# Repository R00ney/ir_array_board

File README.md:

ir_array_board
==============

Eagle files for the ir array board for the NCSU IEEE 2014 SoutheastCon robot

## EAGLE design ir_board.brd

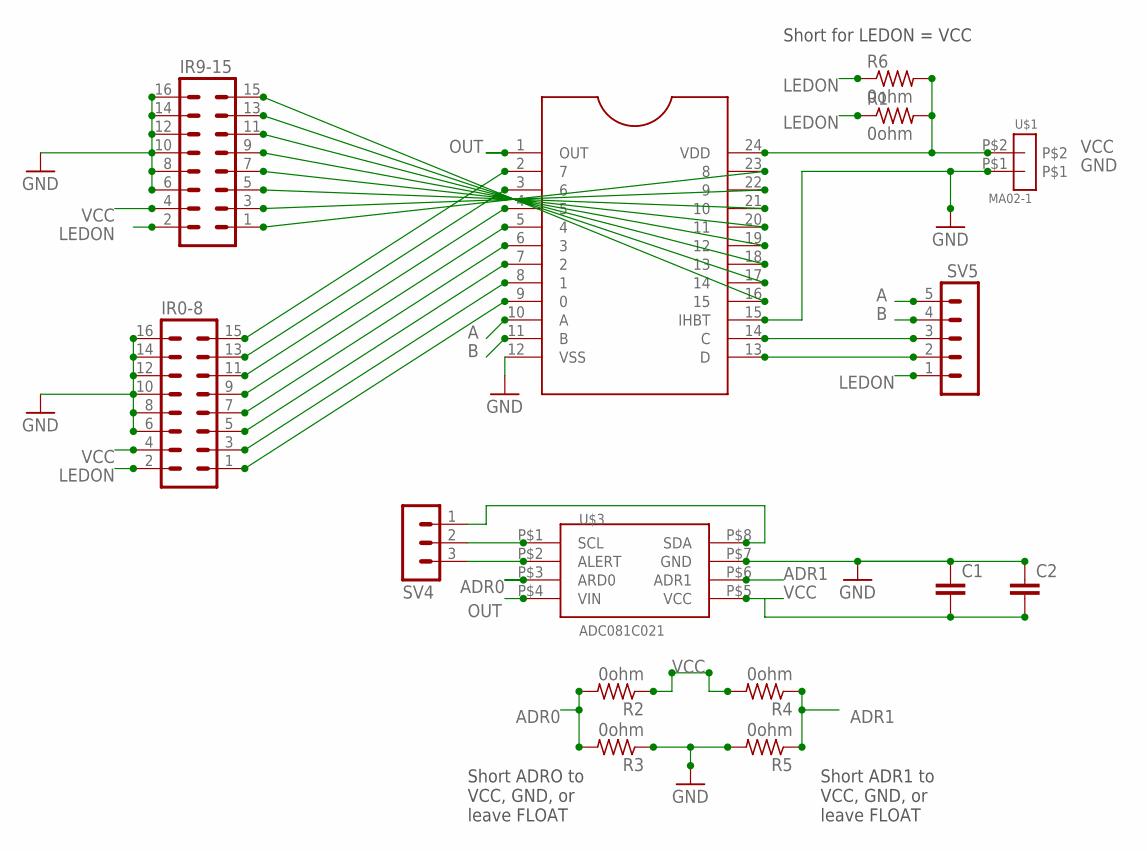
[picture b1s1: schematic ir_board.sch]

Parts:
C1, C2: C-EUC0805K; C0805K
IR0-8, IR9-15: MA08-2
R1, R2, R3, R4, R5, R6: 0ohm; R0805
SV4: MA03-1
SV5: MA05-1
U$1: MA02-1
U$2: 16BIT_ANALOG_MUX; DIL24-6
U$3: ADC081C021; TSSOP-8

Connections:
A: SV5.5, U$2.10 (A)
ADR0: R2.2, R3.2, U$3.P$3 (ARD0)
ADR1: R4.1, R5.1, U$3.P$6 (ADR1)
ALERT: SV4.3, U$3.P$2 (ALERT)
B: SV5.4, U$2.11 (B)
GND: C1.1, C2.1, IR0-8.6, IR0-8.8, IR0-8.10, IR0-8.12, IR0-8.14, IR0-8.16, IR9-15.6, IR9-15.8, IR9-15.10, IR9-15.12, IR9-15.14, IR9-15.16, R3.1, R5.2, U$1.P$1, U$2.12 (VSS), U$2.15 (IHBT), U$3.P$7 (GND)
LEDON: IR0-8.2, IR9-15.2, R1.1, R6.1, SV5.1
unnamed: IR0-8.1, U$2.9 (0)
unnamed: IR0-8.3, U$2.8 (1)
unnamed: IR0-8.5, U$2.7 (2)
unnamed: IR0-8.7, U$2.6 (3)
unnamed: IR0-8.9, U$2.5 (4)
unnamed: IR0-8.11, U$2.4 (5)
unnamed: IR0-8.13, U$2.3 (6)
unnamed: IR0-8.15, U$2.2 (7)
unnamed: IR9-15.1, U$2.23 (8)
unnamed: IR9-15.3, U$2.22 (9)
unnamed: IR9-15.5, U$2.21 (10)
unnamed: IR9-15.7, U$2.20 (11)
unnamed: IR9-15.9, U$2.19 (12)
unnamed: IR9-15.11, U$2.18 (13)
unnamed: IR9-15.13, U$2.17 (14)
unnamed: IR9-15.15, U$2.16 (15)
unnamed: SV5.2, U$2.13 (D)
unnamed: SV5.3, U$2.14 (C)
OUT: U$2.1 (OUT), U$3.P$4 (VIN)
SCL: SV4.2, U$3.P$1 (SCL)
SDA: SV4.1, U$3.P$8 (SDA)
VCC: C1.2, C2.2, IR0-8.4, IR9-15.4, R1.2, R2.1, R4.2, R6.2, U$1.P$2, U$2.24 (VDD), U$3.P$5 (VCC)

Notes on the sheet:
Short for LEDON = VCC
Short ADRO to VCC, GND, or leave FLOAT
Short ADR1 to VCC, GND, or leave FLOAT

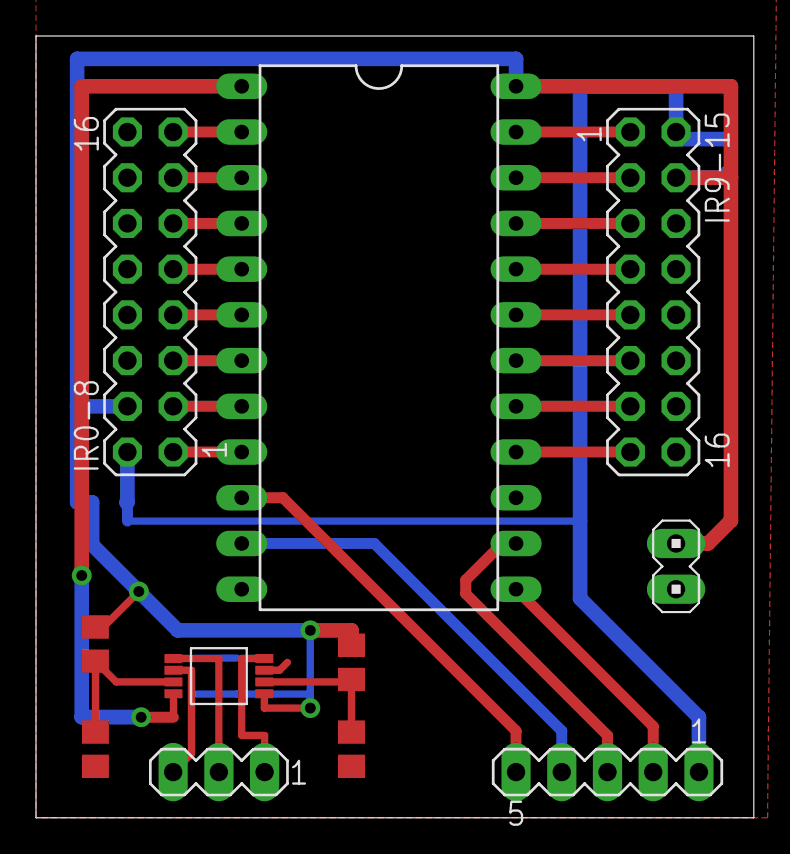
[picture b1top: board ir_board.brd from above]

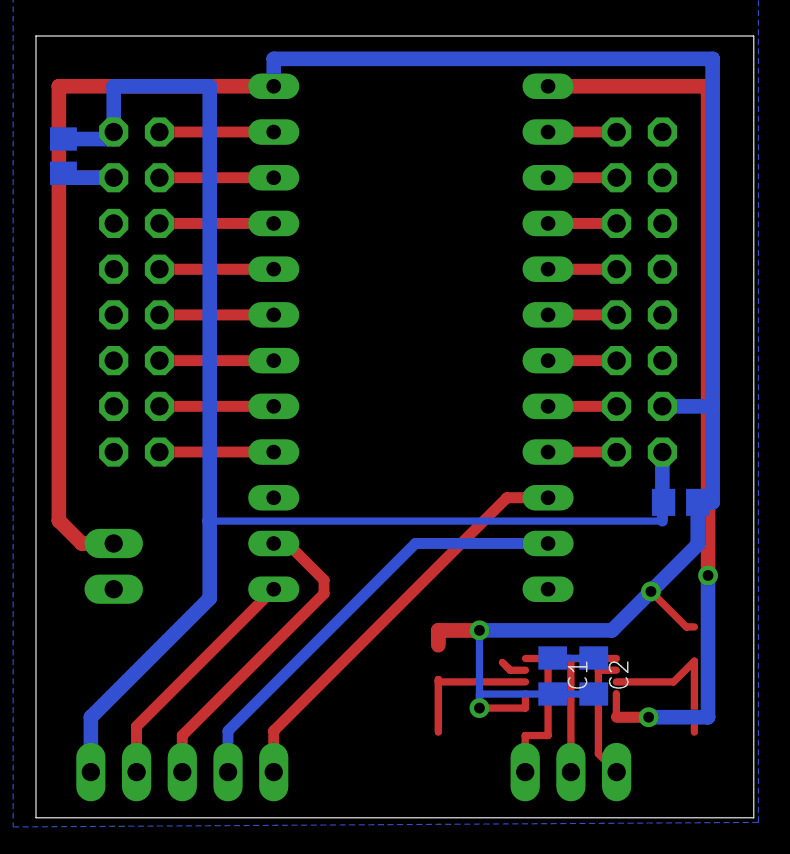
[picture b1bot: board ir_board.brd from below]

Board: 2 copper layers, 39.9 x 43.4 mm, 15 parts (4 on the bottom side), 29 nets.

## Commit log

2013-12-29 Small ir board, no mount holes
2014-01-08 Added debounce caps
2014-01-08 added mounting holes
2014-01-08 Add CAM job for gerbers and a quick makefile
2014-01-08 Add gerbmerge configuration for paneling
2014-01-08 Changed mount holes to vias
2014-01-10 Simplify select line routing and increase clearance
2014-01-10 Don't delete *.bor files
